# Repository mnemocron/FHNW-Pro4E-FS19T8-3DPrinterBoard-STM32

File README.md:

# FHNW-Pro4E-FS19T8-3DPrinterBoard-STM32

Marlin 2.0 compatible 3D printer board based on STM32F103.
Made for the Creality Ender 3 Pro mechanical frame.
Uses TMC2660 with StallGuard for sensorless homing on X and Y axis.

---

FHNW School of Engineering

Elektro- und Informationstechnik (EIT)

FS 2019 - Projekt 4 - Team 8

#### Abstract

> This report documents the development of a controller board and the adaptation of an open source ﬁrmware for a common hobbyist 3D printer. The innovative aspects of this hard- and software development are the usage of a 32-bit microcontroller as well as implementing a web interface for remote access. Part of the research included the incorporation of high-end stepper motor drivers, which detect a motor stall, thereby enabling a sensorless homing of the printer’s axes. A Creality Ender 3 Pro provided the mechanical elements of the printer hardware. The mainboard was built around an STM32F103 microcontroller with an ARM Cortex-M3 core.
TMC2660 drivers were used to drive the motors of the three axes (x, y, z) as well as the extruder. Furthermore, Wi-Fi compatibility was achieved by embedding an ESP32-WROOM-32 module on the mainboard. Every feature of the 3D printer, including the upload of G-code ﬁles, can be controlled through the ESP3D ﬁrmware, which provides a web interface. Since the main processor uses a 32-bit architecture, the development branch of the Marlin ﬁrmware 2.0 was used. Additionally, the newly implemented over-the-air update feature can be used to conveniently upload the latest version of the Marlin ﬁrmware to the microcontroller. The use of the stall detection feature of the TMC2660 motor drivers proved to be feasible in order to omit mechanical limit switches on the x- and y-axis. On the z-axis, however, the stall detection feature showed to be too unreliable. Finally, the Marlin 2.0 ﬁrmware is in a working state
and the use of 32-bit microcontrollers is recommended for future developments of 3D printer hardware.

#### Keywords
> 3D printer ﬁrmware, Wi-Fi web interface, sensorless homing, motor stall detection, over-the-air update, Ender 3 Pro, StallGuard

Based on the `stm32 stm32F103ZEt6`

---

## 💾 Marlin Firmware

Marlin 2.0 Software is in a separate repository.

[MuellerDominik/Marlin](https://github.com/MuellerDominik/Marlin)

---

## 📖 Documentation (German)

Documentation in German is in a seperate repository.

[marco-0909/Pro4_Fachbericht](https://github.com/marco-0909/Pro4_Fachbericht)

---

## ⚠️ Hardware Issues

- wrong Footprint for NPN Transistors in ESP32 reset circuit

The SOT-23 footprint does not match the pinout of the transistor.

- Schematic Error on the LM2675M-x chips

The ON/!OFF pin (pin 5) on both DCDC converters must not be connected to 24V! The pin can only handle 6V. This pin can be left floating.

- The USB type-C receptable can only be soldered using a reflow oven

---

## License

GNU GPLv3

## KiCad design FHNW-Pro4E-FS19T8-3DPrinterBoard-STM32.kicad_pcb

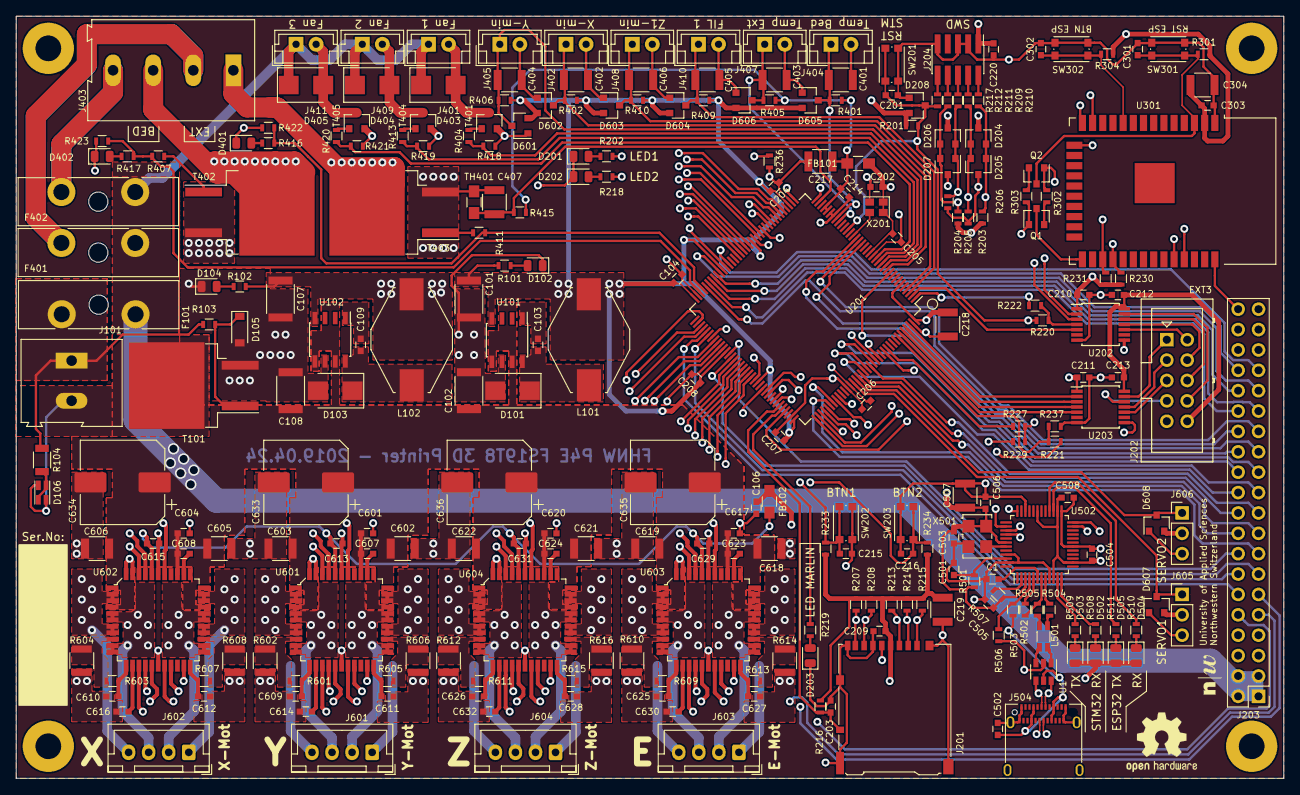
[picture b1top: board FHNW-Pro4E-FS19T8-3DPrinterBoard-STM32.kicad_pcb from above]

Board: 4 copper layers, 158.0 x 95.0 mm, 264 parts (0 on the bottom side), 212 nets.

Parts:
C1: 33n; C_0603
C101, C107: 100uF; C_1812
C102, C108: 330uF; C_1812
C103, C109: 0.01uF/50V; C_0603
C104, C106, C201, C202, C203, C204, C205, C206, C207, C208, C209, C210, C211, C212, C213, C215, C216, C220, C301, C302, C303, C501, C502, C503, C504, C505, C506, C508, C601, C604, C609, C610, C611, C612, C613, C615, C617, C620, C625, C626, C627, C628, C629, C631: 100n; C_0603
C214: 10n; C_0603
C217: 1u; C_1210
C218, C219, C304, C401, C402, C403, C404, C405, C406, C407, C507, C602, C603, C605, C606, C618, C619, C621, C622: 10u; C_1210
C607, C608, C623, C624: 220n; C_0603
C614, C616, C630, C632: 470n; C_0603
C633, C634, C635, C636: 470u; CP_Elec_10x10
D101, D103, D403, D404, D405: Shottky STPS1L30A; D_SMB
D102, D104, D201: LED_GRN; LED_0805_2012Metric
D105: BZT52H-B7V5; D_SOD-123
D106: APHBM2012LSURKZGKC; LED_Kingbright_SMD4_2.0x1.25
D202, D203, D401, D402, D502, D503, D504, D505: LED_YEL; LED_0805_2012Metric
D204, D206: BAT54C; SOT-23
D205, D207: BAT54A; SOT-23
D208, D601, D602, D603, D604, D605, D606, D607, D608: BAT54S; SOT-23
F101: Fuse_20A; Fuseholder_Blade_ATO_Littelfuse_Pudenz_2_Pin
F401: Fuse_3A; Fuseholder_Blade_ATO_Littelfuse_Pudenz_2_Pin
F402: Fuse_10A; Fuseholder_Blade_ATO_Littelfuse_Pudenz_2_Pin
FB101, FB102: Ferrite; R_0805_HandSoldering
G101: SYM_Serial_No; Label_Serial_Number_6x20
G102: SYM_FHNW_Logo; Logo_FHNW_03x05mm
H101, H102, H103, H104: MountingHole; MountingHole_3.2mm_M3_Pad
J101: Screw_Terminal_01x02; TerminalBlock_Altech_AK300-2_P5.00mm
J201: Micro_SD_Card_Det; microSD_HC_Hirose_DM3AT-SF-PEJM5
J202: Conn_02x05_Odd_Even; Multicomp_MC9A12-1034_2x05_P2.54mm_Vertical
J203: Conn_02x20_Odd_Even; PinHeader_2x20_P2.54mm_Vertical
J204: Conn_ARM_JTAG_SWD_10; PinHeader_2x05_P1.27mm_Vertical_SMD
J401, J402, J404, J405, J407, J408, J409, J410, J411: Conn_01x02; JST_EH_B02B-EH-A_02x2.50mm_Straight
J403: Screw_Terminal_01x04; TerminalBlock_Altech_AK300-4_P5.00mm
J504: USB_C_Receptacle; USB_C_Receptacle_Amphenol_12401610E4-2A
J601, J602, J603, J604: B4B-XH-A; JST_XH_B4B-XH-A_1x04_P2.50mm_Vertical
J605, J606: Conn_01x03; PinHeader_1x03_P2.54mm_Vertical
L101, L102: 47uH DO3316-473; L_Fastron_PISN_Handsoldering
L501: WE-744232090; WURTH_USB_Chocke_4PAD
LOGO101: OSHW-LOGOM-COPPER; OSHW-Logo2_9.8x8mm_SilkScreen
Q1, Q2: 2N3904; SOT-23
R101, R102, R202, R218, R219, R416, R417, R508, R509, R510, R511: 330R; R_0603
R103, R418, R419, R421, R422, R423: 100k; R_0603
R104: 10k; R_1206
R201, R203, R204, R205, R206, R207, R208, R213, R214, R215, R216, R230, R231, R233, R234, R236, R237, R301, R302, R303, R304, R402, R406, R407, R409, R410, R411, R506, R507: 10k; R_0603
R209, R210, R211, R212, R217: 100R; R_0603
R220, R221, R222, R227, R229: 0R; R_0603
R401, R405, R415, R503: 4k7; R_0603
R404, R413, R420: 180R; R_0603
R501: 470R; R_0603
R502: 1k5; R_0603
R504, R505: 27R; R_0603
R601, R603, R605, R607, R609, R611, R613, R615: 10R; R_0603
R602, R604, R606, R608, R610, R612, R614, R616: 0R15; R_1210
SW201, SW202, SW203, SW301, SW302: SW_Push; SW_SPST_KMR2
T101, T402, T403: BUK963R3-60E; TO-263-2
T401, T404, T405: PMV40UN2; SOT-23
TH401: Thermistor_NTC; R_0805_HandSoldering
U1: USBLC6-2SC6; SOT-23-6
U101: LM2675M-3.3; SOIC-8_3.9x4.9mm_P1.27mm
U102: LM2675M-5; SOIC-8_3.9x4.9mm_P1.27mm
U201: STM32F103ZETx; LQFP-144_20x20mm_Pitch0.5mm
U202, U203: NTS0104PW-Q100J; TSSOP-14_4.4x5mm_Pitch0.65mm
U301: ESP32-WROOM-32
U502: FT2232D; LQFP-48_7x7mm_P0.5mm
U601, U602, U603, U604: TMC2660; TQFP-44_10x10mm
X201: SG-210STF; Oscillator_SMD_SeikoEpson_SG210-4Pin_2.5x2.0mm
X501: SG5032CCN-6.000000M-HJGA3; Oscillator_SMD_SeikoEpson_SG8002LB-4Pin_5.0x3.2mm

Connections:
+3.3VA: C214.1, C217.1, FB101.1, R401.1, R405.1, R415.1, U201.32, U201.33
+3.3VP: C613.1, C615.1, C629.1, C631.1, FB102.1, U601.40, U602.40, U603.40, U604.40
+3V3: C101.1, C104.1, C106.1, C202.1, C204.1, C205.1, C206.1, C207.1, C208.1, C209.1, C210.1, C211.1, C218.1, C219.1, C220.1, C303.1, C304.1, C504.1, C508.1, D204.3, D206.3, D208.2, D502.2, D503.2, D504.2, D505.2, D601.2, D602.2, D603.2, D604.2, D605.2, D606.2, D607.2, D608.2, FB101.2, FB102.2, J201.4, J203.7, J203.8, J204.1, J605.2, J606.2, L101.2, R101.1, R201.1, R203.2, R204.2, R207.1, R208.1, R213.1, R214.1, R215.1, R216.2, R230.1, R231.1, R233.1, R234.1, R301.1, R304.1, R402.1, R406.1, R409.1, R410.1, U101.4, U201.6, U201.17, U201.39, U201.52, U201.62, U201.72, U201.84, U201.95, U201.108, U201.121, U201.131, U201.144, U202.1, U202.8, U203.1, U203.8, U301.2, U502.10, U502.14, U502.26, U502.31, X201.1, X201.4
+5V: C107.1, C212.1, C213.1, C503.1, C505.1, C506.1, C507.1, J202.10, L102.2, R102.1, R501.2, R507.1, U102.4, U202.14, U203.14, U502.3, U502.42, X501.1, X501.4
+24V: C102.1, C108.1, C601.1, C602.1, C603.1, C604.1, C605.1, C606.1, C607.1, C608.1, C617.1, C618.1, C619.1, C620.1, C621.1, C622.1, C623.1, C624.1, C633.1, C634.1, C635.1, C636.1, D403.1, D404.1, D405.1, F101.1, F401.2, F402.2, J203.1, J203.2, J203.3, J203.4, J401.1, J409.1, J411.1, U101.5, U101.7, U102.5, U102.7, U601.4, U601.30, U601.36, U602.4, U602.30, U602.36, U603.4, U603.30, U603.36, U604.4, U604.30, U604.36
/24V_GND: D106.1, D106.3, J101.2, T101.2
/24V_IN: F101.2, J101.1, R103.1, R104.1
/appendix_ESP32/ESP32_GPIO0: Q1.3, U301.25
/appendix_ESP32/ESP32_RESET: C301.1, Q2.3, R301.2, SW301.2, U301.3
/appendix_ESP32/ESP_DTR: Q1.1, R303.2, U502.36
/appendix_ESP32/ESP_RTS: Q2.1, R302.2, U502.38
/appendix_ESP32/ESP_RX_STM: R231.2, U201.101, U301.27
/appendix_ESP32/ESP_RX_USB: U301.34, U502.40
/appendix_ESP32/ESP_TX_STM: R230.2, U201.102, U301.28
/appendix_ESP32/ESP_TX_USB: U301.35, U502.39
/appendix_SENSORS_POWER/ADC_TEMP_BED: C401.1, D605.3, J404.1, R401.2, U201.29
/appendix_SENSORS_POWER/ADC_TEMP_E1: C403.1, D606.3, J407.1, R405.2, U201.28
/appendix_SENSORS_POWER/ADC_TEMP_PCB: C407.1, R415.2, TH401.2, U201.35
/appendix_SENSORS_POWER/Bed_pwr: J403.3, T402.2
/appendix_SENSORS_POWER/E1_pwr: J403.1, T403.2
/appendix_SENSORS_POWER/Fan1_pwr: D403.2, J401.2, T401.3
/appendix_SENSORS_POWER/Fan2_pwr: D404.2, J409.2, T404.3
/appendix_SENSORS_POWER/Fan3_pwr: D405.2, J411.2, T405.3
/appendix_SENSORS_POWER/SERVO_1: D607.3, J605.1, U201.122
/appendix_SENSORS_POWER/SERVO_2: D608.3, J606.1, U201.123
/appendix_SENSORS_POWER/SW_End_Filament_1: C405.1, D604.3, J410.1, R409.2, U201.3
/appendix_SENSORS_POWER/SW_End_X: C402.1, D601.3, J402.1, R402.2, U201.11
/appendix_SENSORS_POWER/SW_End_Y: C404.1, D602.3, J405.1, R406.2, U201.12
/appendix_SENSORS_POWER/SW_End_Z: C406.1, D603.3, J408.1, R410.2, U201.4
/appendix_STM32F103/BED_ON: R407.2, R417.2, R423.1, U201.70
/appendix_STM32F103/CS_E1: U201.93, U603.18
/appendix_STM32F103/CS_X: U201.50, U602.18
/appendix_STM32F103/CS_Y: U201.57, U601.18
/appendix_STM32F103/CS_Z1: U201.88, U604.18
/appendix_STM32F103/DIR_E1: U201.90, U603.41
/appendix_STM32F103/DIR_X: U201.42, U602.41
/appendix_STM32F103/DIR_Y: U201.54, U601.41
/appendix_STM32F103/DIR_Z1: U201.81, U604.41
/appendix_STM32F103/E1_ON: R411.2, R416.2, R422.1, U201.69
/appendix_STM32F103/EN_E1: U201.92, U603.19
/appendix_STM32F103/EN_X: U201.49, U602.19
/appendix_STM32F103/EN_Y: U201.56, U601.19
/appendix_STM32F103/EN_Z1: U201.87, U604.19
/appendix_STM32F103/FAN1: R404.2, R418.1, U201.13
/appendix_STM32F103/FAN2: R413.2, R419.1, U201.14
/appendix_STM32F103/FAN3: R420.2, R421.1, U201.15
/appendix_STM32F103/RCC_OSC_IN: U201.23, X201.3
/appendix_STM32F103/STALL_E1: U201.91, U603.38
/appendix_STM32F103/STALL_X: U201.43, U602.38
/appendix_STM32F103/STALL_Y: U201.55, U601.38
/appendix_STM32F103/STALL_Z1: U201.82, U604.38
/appendix_STM32F103/STEP_E1: U201.89, U603.42
/appendix_STM32F103/STEP_X: U201.41, U602.42
/appendix_STM32F103/STEP_Y: U201.53, U601.42
/appendix_STM32F103/STEP_Z1: U201.80, U604.42
/appendix_STM32F103/STM32_BOOT_0: R221.1, U301.14
/appendix_STM32F103/STM32_NRST: R229.1, U301.13
/appendix_STM32F103/STM_BOOT0: R221.2, R237.1, U201.138
/appendix_STM32F103/STM_BOOT1: R236.1, U201.48
/appendix_TMC2660_X/MOT_E1_A1: J603.4, U603.2, U603.3, U603.7, U603.8
/appendix_TMC2660_X/MOT_E1_A2: J603.3, U603.5, U603.6, U603.10, U603.11
/appendix_TMC2660_X/MOT_E1_B1: J603.1, U603.26, U603.27, U603.31, U603.32
/appendix_TMC2660_X/MOT_E1_B2: J603.2, U603.23, U603.24, U603.28, U603.29
/appendix_TMC2660_X/MOT_X_A1: J602.4, U602.2, U602.3, U602.7, U602.8
/appendix_TMC2660_X/MOT_X_A2: J602.3, U602.5, U602.6, U602.10, U602.11
/appendix_TMC2660_X/MOT_X_B1: J602.1, U602.26, U602.27, U602.31, U602.32
/appendix_TMC2660_X/MOT_X_B2: J602.2, U602.23, U602.24, U602.28, U602.29
/appendix_TMC2660_X/MOT_Y_A1: J601.4, U601.2, U601.3, U601.7, U601.8
/appendix_TMC2660_X/MOT_Y_A2: J601.3, U601.5, U601.6, U601.10, U601.11
/appendix_TMC2660_X/MOT_Y_B1: J601.1, U601.26, U601.27, U601.31, U601.32
/appendix_TMC2660_X/MOT_Y_B2: J601.2, U601.23, U601.24, U601.28, U601.29
/appendix_TMC2660_X/MOT_Z1_A1: J604.4, U604.2, U604.3, U604.7, U604.8
/appendix_TMC2660_X/MOT_Z1_A2: J604.3, U604.5, U604.6, U604.10, U604.11
/appendix_TMC2660_X/MOT_Z1_B1: J604.1, U604.26, U604.27, U604.31, U604.32
/appendix_TMC2660_X/MOT_Z1_B2: J604.2, U604.23, U604.24, U604.28, U604.29
/appendix_UART_USB/FT_RX_A: U201.36, U502.23
/appendix_UART_USB/FT_TX_A: U201.37, U502.24
/appendix_UART_USB/USB_D_N: J504.A7, J504.B7, U1.6
/appendix_UART_USB/USB_D_P: J504.A6, J504.B6, U1.4
/appendix_UART_USB/USB_FT_D_N: R504.1, U502.8
/appendix_UART_USB/USB_FT_D_P: R502.2, R505.1, U502.7
/appendix_UART_USB/USB_SUP_D_N: L501.3, R504.2
/appendix_UART_USB/USB_SUP_D_P: L501.2, R505.2
/appendix_UART_USB/USB_TVS_D_N: L501.4, U1.1
/appendix_UART_USB/USB_TVS_D_P: L501.1, U1.3
/appendix_UART_USB/XTAL_FTDI: U502.43, X501.3
ADC_TEMP_EXT: J203.27, U201.21
BTN_USER_1: C215.1, R233.2, SW202.2, U201.79
BTN_USER_2: C216.1, R234.2, SW203.2, U201.97
E2_ADC_TEMP: J203.26, U201.22
E2_CS: J203.14, U201.78
E2_DIR: J203.18, U201.115
E2_EN: J203.20, U201.125
E2_END_FIL: J203.24, U201.129
E2_FAN1: J203.30, U201.67
E2_FAN2: J203.32, U201.65
E2_HOTEND: J203.34, U201.63
E2_STALL: J203.22, U201.126
E2_STEP: J203.16, U201.85
E3_ADC_TEMP: J203.25, U201.20
E3_CS: J203.13, U201.86
E3_DIR: J203.17, U201.124
E3_EN: J203.19, U201.128
E3_END_FIL: J203.23, U201.10
E3_STALL: J203.21, U201.127
E3_STEP: J203.15, U201.114
EXP3_LCD_Beeper: J202.1, U203.13
EXP3_LCD_CS: J202.7, U203.12
EXP3_LCD_Encoder_A: J202.5, U203.10
EXP3_LCD_Encoder_B: J202.3, U203.11
EXP3_LCD_Encoder_BTN: J202.2, U202.10
EXP3_LCD_MOSI: J202.8, U202.13
EXP3_LCD_Reset: J202.4, U202.11
EXP3_LCD_SCK: J202.6, U202.12
FAN_EXT: J203.28, U201.68
GND: C1.1, C101.2, C102.2, C104.2, C106.2, C107.2, C108.2, C201.2, C202.2, C203.2, C204.2, C205.2, C206.2, C207.2, C208.2, C209.2, C210.2, C211.2, C212.2, C213.2, C214.2, C215.2, C216.2, C217.2, C218.2, C219.2, C220.2, C301.2, C302.2, C303.2, C304.2, C401.2, C402.2, C403.2, C404.2, C405.2, C406.2, C407.2, C501.2, C502.2, C503.2, C504.2, C505.2, C506.2, C507.2, C508.2, C601.2, C602.2, C603.2, C604.2, C605.2, C606.2, C609.1, C610.1, C611.1, C612.1, C613.2, C614.2, C615.2, C616.2, C617.2, C618.2, C619.2, C620.2, C621.2, C622.2, C625.1, C626.1, C627.1, C628.1, C629.2, C630.2, C631.2, C632.2, C633.2, C634.2, C635.2, C636.2, D101.2, D102.1, D103.2, D104.1, D105.2, D201.1, D202.1, D203.1, D205.3, D207.3, D208.1, D401.1, D402.1, D601.1, D602.1, D603.1, D604.1, D605.1, D606.1, D607.1, D608.1, J201.6, J201.9, J201.11, J202.9, J203.35, J203.36, J203.37, J203.38, J203.39, J203.40, J204.3, J204.5, J204.9, J402.2, J404.2, J405.2, J407.2, J408.2, J410.2, J504.A1, J504.A12, J504.B1, J504.B12, J504.S1, J605.3, J606.3, R205.1, R206.1, R236.2, R237.2, R418.2, R419.2, R421.2, R422.2, R423.2, R506.1, R602.1, R604.1, R606.1, R608.1, R610.1, R612.1, R614.1, R616.1, SW201.1, SW202.1, SW203.1, SW301.1, SW302.1, T101.3, T401.2, T402.3, T403.3, T404.2, T405.2, TH401.1, U1.2, U101.6, U102.6, U201.16, U201.30, U201.31, U201.38, U201.51, U201.61, U201.71, U201.83, U201.94, U201.107, U201.120, U201.130, U201.143, U202.7, U203.7, U301.1, U301.15, U301.38, U502.9, U502.18, U502.25, U502.34, U502.45, U502.47, U601.17, U601.21, U601.39, U601.43, U601.44, U602.17, U602.21, U602.39, U602.43, U602.44, U603.17, U603.21, U603.39, U603.43, U603.44, U604.17, U604.21, U604.39, U604.43, U604.44, X201.2, X501.2
GPIO_EXT_0: J203.12, U201.77
GPIO_EXT_1: J203.29, U201.66
GPIO_EXT_2: J203.31, U201.64
GPIO_EXT_3: J203.33, U201.60
JTAG_RESET: C201.1, D208.3, R201.2, R217.2, R220.2, R227.2, R229.2, SW201.2, U201.25
JTAG_TCK_SWCLK: D204.1, D205.2, R205.2, R209.2, U201.109
JTAG_TDI: D206.1, D207.2, R204.1, R212.2, U201.110
JTAG_TDO_SWO: D206.2, D207.1, R206.2, R211.2, U201.133
JTAG_TMS_SWDIO: D204.2, D205.1, R203.1, R210.2, U201.105
JTAG_TRST: R227.1, U201.134
LCD_BUZZER: U201.142, U203.2
LCD_CS: U201.141, U203.3
LCD_ENC_A: U201.139, U203.5
LCD_ENC_B: U201.140, U203.4
LCD_ENC_BTN: U201.2, U202.5
LCD_Reset: R220.1, R222.1, U202.4
LED_Marlin: R219.1, U201.104
LED_USER_1: R202.1, U201.45
LED_USER_2: R218.1, U201.46
MISO: J203.10, U201.75, U601.14, U602.14, U603.14, U604.14
MOSI: J203.9, U201.76, U202.2, U601.15, U602.15, U603.15, U604.15
unnamed: C1.2, U502.6
unnamed: C103.1, U101.1
unnamed: C103.2, D101.1, L101.1, U101.8
unnamed: C109.1, U102.1
unnamed: C109.2, D103.1, L102.1, U102.8
unnamed: C302.1, R304.2, SW302.2, U301.10
unnamed: C501.1, R501.1, U502.46
unnamed: C607.2, U601.35
unnamed: C608.2, U602.35
unnamed: C609.2, R601.2, U601.12
unnamed: C610.2, R603.2, U602.12
unnamed: C611.2, R605.2, U601.22
unnamed: C612.2, R607.2, U602.22
unnamed: C614.1, U601.13
unnamed: C616.1, U602.13
unnamed: C623.2, U603.35
unnamed: C624.2, U604.35
unnamed: C625.2, R609.2, U603.12
unnamed: C626.2, R611.2, U604.12
unnamed: C627.2, R613.2, U603.22
unnamed: C628.2, R615.2, U604.22
unnamed: C630.1, U603.13
unnamed: C632.1, U604.13
unnamed: D102.2, R101.2
unnamed: D104.2, R102.2
unnamed: D105.1, R103.2, T101.1
unnamed: D106.2, D106.4, R104.2
unnamed: D201.2, R202.2
unnamed: D202.2, R218.2
unnamed: D203.2, R219.2
unnamed: D401.2, R416.1
unnamed: D402.2, R417.1
unnamed: D502.1, R508.2
unnamed: D503.1, R509.2
unnamed: D504.1, R510.2
unnamed: D505.1, R511.2
unnamed: F401.1, J403.2
unnamed: F402.1, J403.4
unnamed: J204.2, R210.1
unnamed: J204.4, R209.1
unnamed: J204.6, R211.1
unnamed: J204.8, R212.1
unnamed: J204.10, R217.1
unnamed: Q1.2, R302.1
unnamed: Q2.2, R303.1
unnamed: R222.2, U201.1
unnamed: R404.1, T401.1
unnamed: R407.1, T402.1
unnamed: R411.1, T403.1
unnamed: R413.1, T404.1
unnamed: R420.1, T405.1
unnamed: R502.1, U502.5
unnamed: R503.1, R506.2, U502.4
unnamed: R507.2, U502.2
unnamed: R601.1, R602.2, U601.9
unnamed: R603.1, R604.2, U602.9
unnamed: R605.1, R606.2, U601.25
unnamed: R607.1, R608.2, U602.25
unnamed: R609.1, R610.2, U603.9
unnamed: R611.1, R612.2, U604.9
unnamed: R613.1, R614.2, U603.25
unnamed: R615.1, R616.2, U604.25
SCK: J203.11, U201.74, U202.3, U601.16, U602.16, U603.16, U604.16
SD_CLK: J201.5, U201.113
SD_CMD: J201.3, R213.2, U201.116
SD_DAT0: J201.7, R208.2, U201.98
SD_DAT1: J201.8, R207.2, U201.99
SD_DAT2: J201.1, R215.2, U201.111
SD_DAT3: J201.2, R214.2, U201.112
SD_DETECT: C203.1, J201.10, R216.1, U201.103
UART1_RX_LED: R508.1, U502.12
UART1_TX_LED: R509.1, U502.11
UART2_RX_LED: R510.1, U502.28
UART2_TX_LED: R511.1, U502.27
VBUS: C502.1, J504.A4, J504.A9, J504.B4, J504.B9, R503.2, U1.5

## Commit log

2019-04-02 created hierarchical .sch files added library with TMC2660 and BUK963 copied schematics for TMC2660 and various sensors/power in/out
2019-04-03 added FTDI chip
2019-04-03 merged hierarchical schematics
2019-04-06 5V Speisung entfernt und durch 5V von USB ersetzt
2019-04-06 Display hinzugefügt
2019-04-09 pre Annotation 1
2019-04-09 1st annotation, footprints, netlist
2019-04-09 started layouting TMC2660
2019-04-12 Layout: all TMC / Schematic: Oli's comments
2019-04-12 Printed Schematic for review process
2019-04-13 added footprints, layouted 3v3 Reg
2019-04-13 added LEDs
2019-04-16 corrected P.S. Schematic review
2019-04-19 added FT2232 by Marco M
2019-04-21 fixed missing symbol issue fixed 3vout cap on FTDI
2019-04-22 started with STM32 Pinout connections (Mittagspause)
2019-04-22 layouted FT2232 / SD card
2019-04-22 added cache.lib to git
2019-04-22 cleaned up Layout
2019-04-23 Layout update
2019-04-23 having issues with netclasses
2019-04-23 Layoutet Power 3.3V / 5V
2019-04-23 first layout draft without 40pin
2019-04-24 user LED + fixes in Layout
2019-04-24 TVS protection, BOOT1 pin, user BTN
2019-04-24 finished up for final review
2019-04-24 fixed minor layout stuff with mueller
2019-04-25 changed screw terminal for bed/ext
2019-04-25 changed Layout to use all Interrupt Pins
2019-04-25 fixed last minor issues
2019-04-25 printed PDF and Gerbers
2019-04-25 fixed minimum clearance of 0.125mm
2019-04-25 increased size of USB Pad
2019-04-25 Create OSHW compatible license
2019-04-25 edit README, remove unnecessary files
2019-05-03 Added comments to the schematic. Changed various component values (annotated only).
2019-05-05 created assembly instructions
2019-05-10 added draft of abstract
2019-05-10 added comments from comments branch corrected silk Servo2 added title to schematic pages
2019-05-10 3d rendering + readme I probably broke the 3D rendering for others because of hardcoded paths to 3d shapes > works on my machine ¯\_(ツ)_/¯
2019-05-10 fix stm logo
2019-05-13 clarified some component values and printed PDFs
2019-06-20 explained hardware issues and clarified README
